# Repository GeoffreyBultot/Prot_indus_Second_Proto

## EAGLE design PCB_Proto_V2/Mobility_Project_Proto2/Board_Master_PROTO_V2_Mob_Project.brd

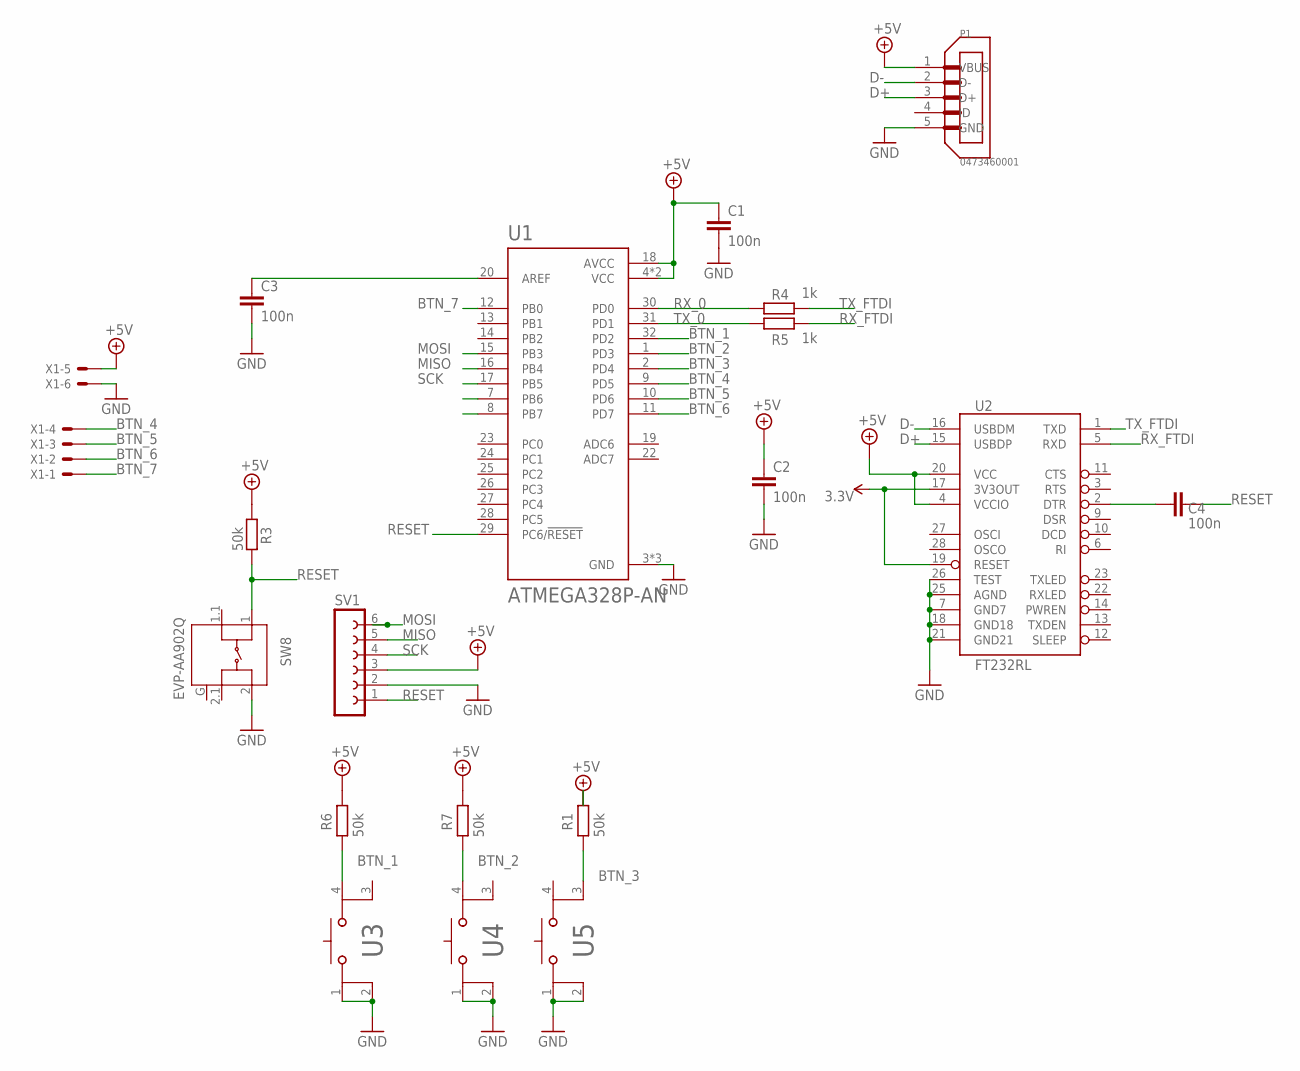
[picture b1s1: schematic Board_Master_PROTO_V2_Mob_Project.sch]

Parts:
C1, C2, C3, C4: 100n; CAP_0805
P1: 0473460001; MOLEX_0473460001
R1, R3, R6, R7: 50k; R0805
R4, R5: 1k; R0805
SV1: FE06-1; FE06
SW8: EVP-AA902Q
U1: ATMEGA328P-AN; QFP80P900X900X120-32N
U2: FT232RL; SSOP28DB
U3, U4, U5: 4-1437565-1; SW4_236X236H5MM
X1: C-GRID-06-70543; 70543-06

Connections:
3.3V: U2.17 (3V3OUT), U2.19 (RESET)
+5V: C1.1, C2.1, P1.1 (VBUS), R1.1, R3.1, R6.1, R7.1, SV1.3, U1.4 (VCC), U1.6 (VCC), U1.18 (AVCC), U2.4 (VCCIO), U2.20 (VCC), X1.5
BTN_1: R6.2, U1.32 (PD2), U3.4
BTN_2: R7.2, U1.1 (PD3), U4.4
BTN_3: R1.2, U1.2 (PD4), U5.3
BTN_4: U1.9 (PD5), X1.4
BTN_5: U1.10 (PD6), X1.3
BTN_6: U1.11 (PD7), X1.2
BTN_7: U1.12 (PB0), X1.1
D+: P1.3 (D+), U2.15 (USBDP)
D-: P1.2 (D-), U2.16 (USBDM)
GND: C1.2, C2.2, C3.2, P1.5 (GND), SV1.2, SW8.2, U1.3 (GND), U1.5 (GND), U1.21 (GND), U2.7 (GND7), U2.18 (GND18), U2.21 (GND21), U2.25 (AGND), U2.26 (TEST), U3.1, U3.2, U4.1, U4.2, U5.1, U5.2, X1.6
MISO: SV1.5, U1.16 (PB4)
MOSI: SV1.6, U1.15 (PB3)
unnamed: C4.2, U2.2 (DTR)
unnamed: C3.1, U1.20 (AREF)
RESET: C4.1, R3.2, SV1.1, SW8.1, U1.29 (PC6/!RESET)
RX_0: R4.1, U1.30 (PD0)
RX_FTDI: R5.2, U2.5 (RXD)
SCK: SV1.4, U1.17 (PB5)
TX_0: R5.1, U1.31 (PD1)
TX_FTDI: R4.2, U2.1 (TXD)

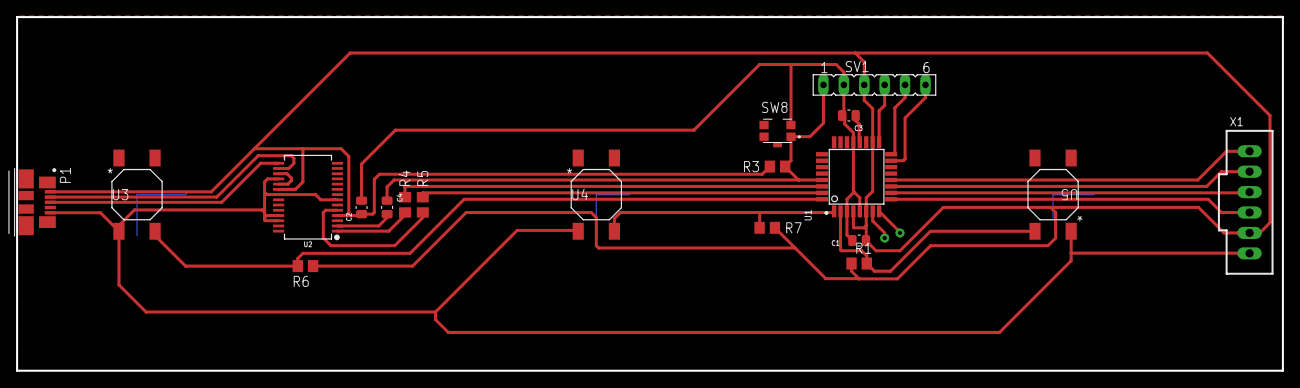
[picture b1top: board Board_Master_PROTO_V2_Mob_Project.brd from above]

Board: 2 copper layers, 157.5 x 44.0 mm, 19 parts (0 on the bottom side), 22 nets.

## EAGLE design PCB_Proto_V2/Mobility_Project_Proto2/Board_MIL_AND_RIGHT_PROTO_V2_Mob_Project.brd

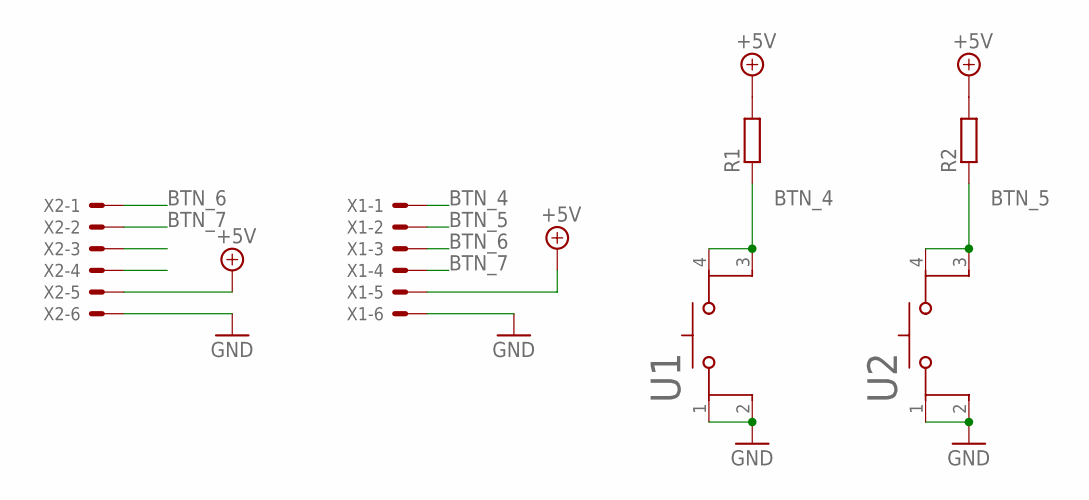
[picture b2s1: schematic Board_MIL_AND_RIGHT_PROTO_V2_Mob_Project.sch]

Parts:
R1, R2: R-EU_M0805; M0805
U1, U2: 4-1437565-1; SW4_236X236H5MM
X1, X2: C-GRID-06-70543; 70543-06

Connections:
+5V: R1.2, R2.2, X1.5, X2.5
BTN_4: R1.1, U1.3, U1.4, X1.1
BTN_5: R2.1, U2.3, U2.4, X1.2
BTN_6: X1.3, X2.1
BTN_7: X1.4, X2.2
GND: U1.1, U1.2, U2.1, U2.2, X1.6, X2.6

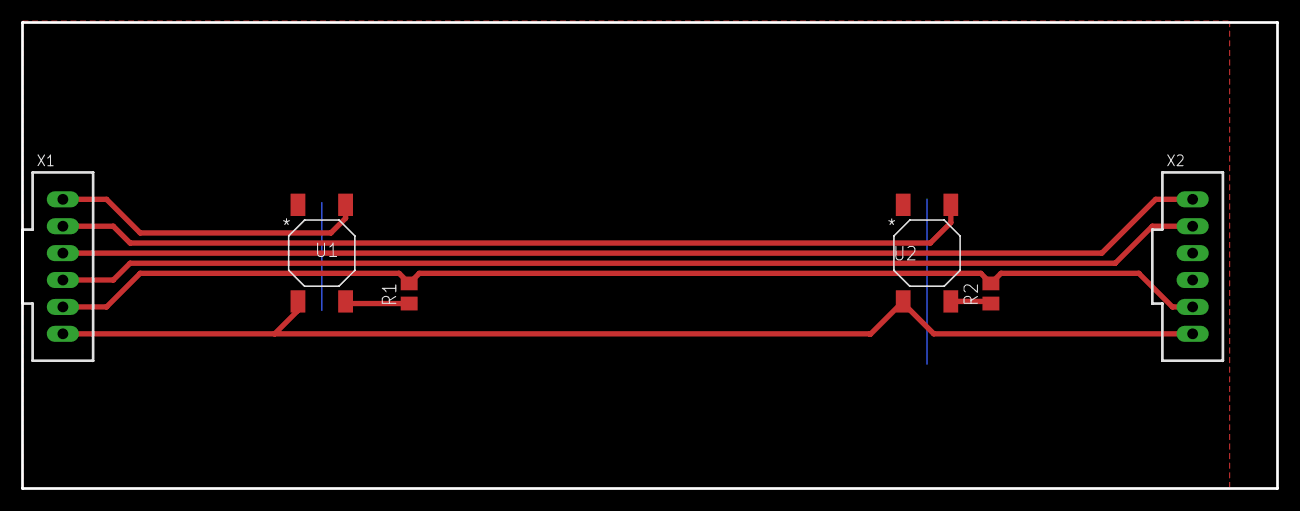
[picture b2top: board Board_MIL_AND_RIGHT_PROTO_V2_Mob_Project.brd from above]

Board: 2 copper layers, 118.5 x 44.0 mm, 6 parts (0 on the bottom side), 6 nets.

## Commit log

2019-12-14 First Commit
    d
2019-12-14 add arduino and PCB
2019-12-15 ajout 3D

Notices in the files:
parts and their libraries:
COPYRIGHT: Copyright (C) 2016 Accelerated Designs. All rights reserved
SparkFun-IC-Comms: Licensing: Creative Commons ShareAlike 4.0 International - https://creativecommons.org/licenses/by-sa/4.0
